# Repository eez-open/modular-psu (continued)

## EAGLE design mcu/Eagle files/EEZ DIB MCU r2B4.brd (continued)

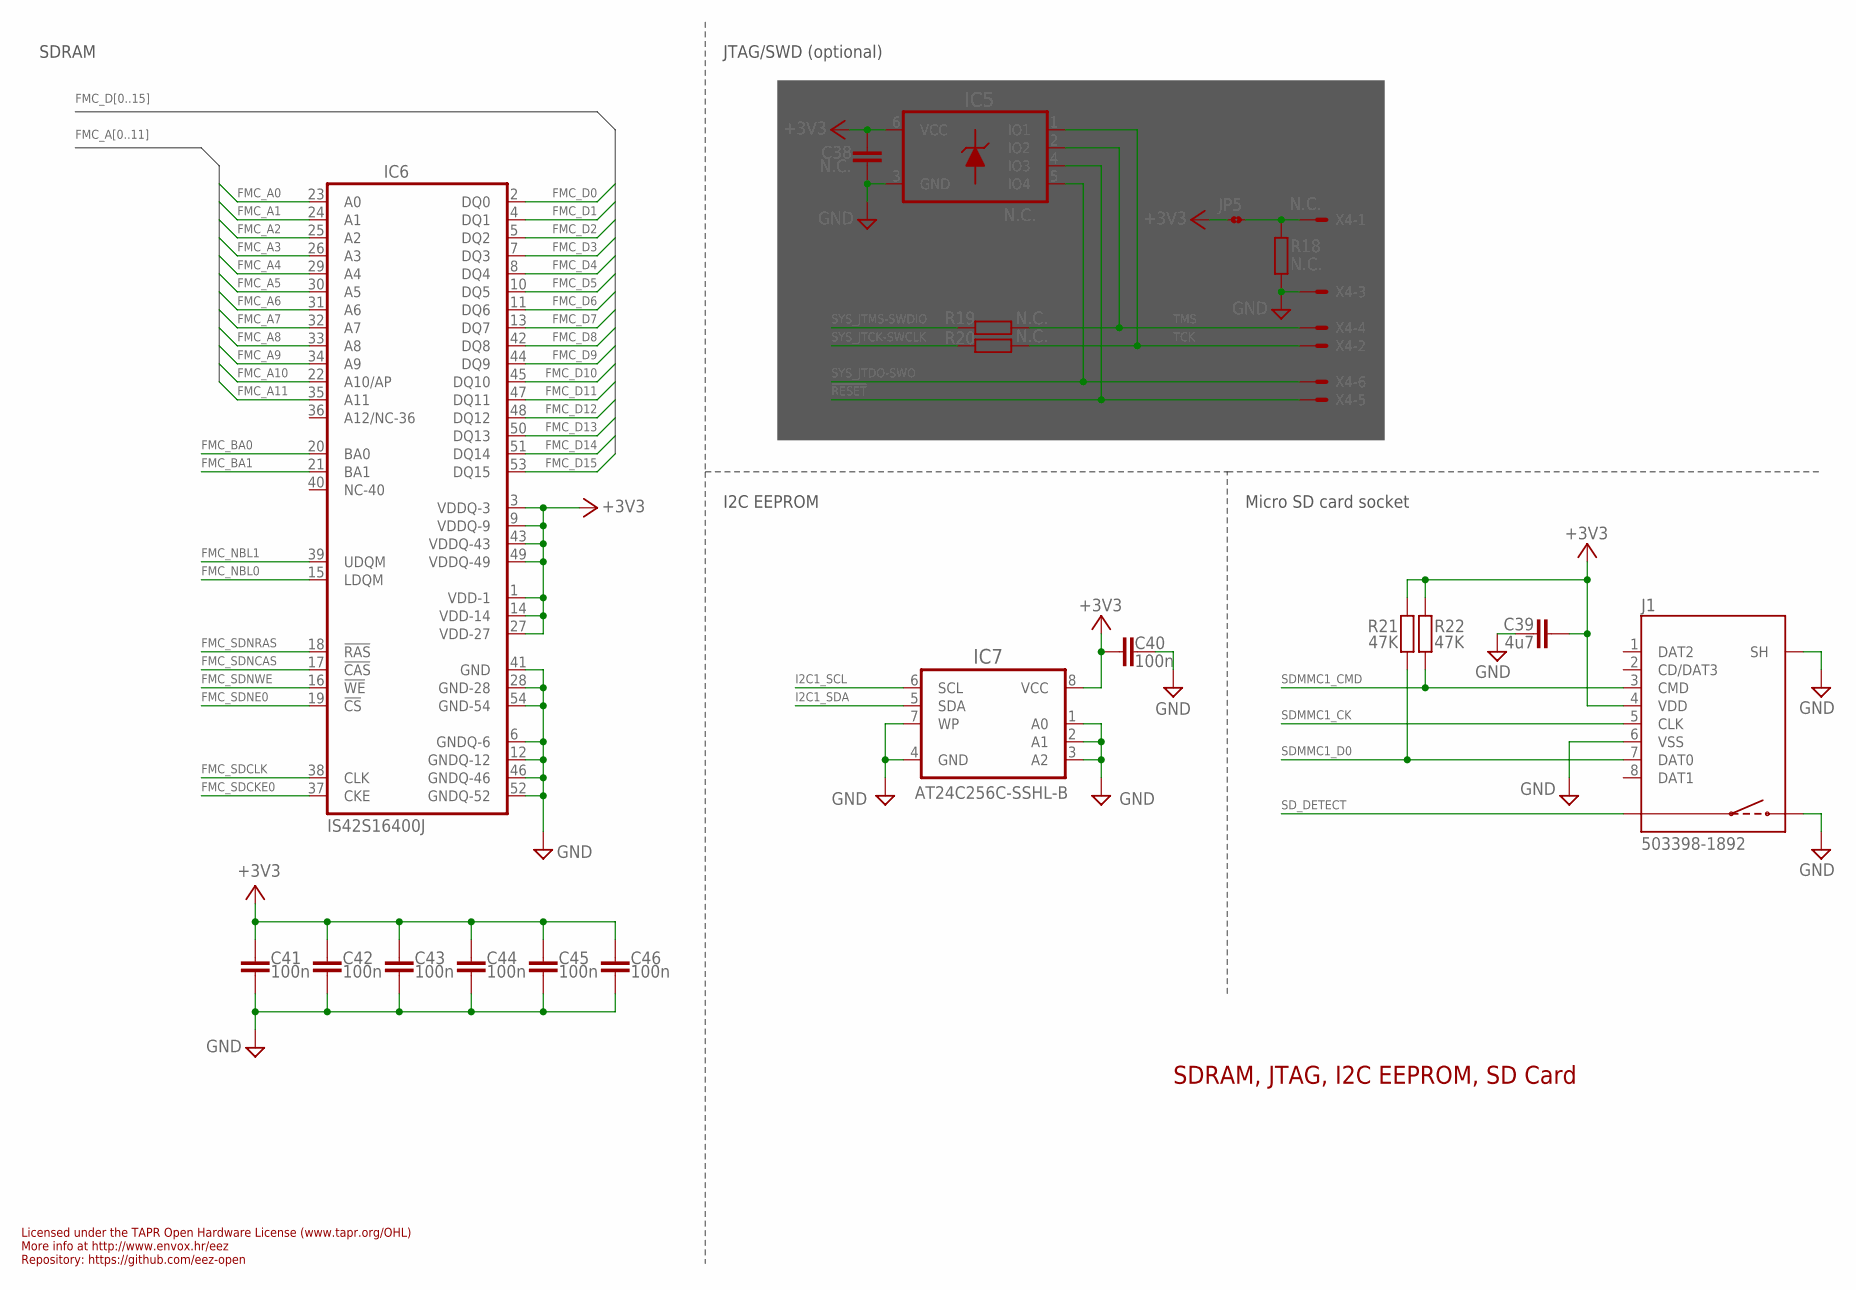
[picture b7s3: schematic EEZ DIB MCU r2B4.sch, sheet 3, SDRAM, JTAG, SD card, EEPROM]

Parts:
C38: N.C.; C0603
C39: 4u7; C1206
C40, C41, C42, C43, C44, C45, C46: 100n; C0603
IC5: N.C.; DRL6
IC6: IS42S16400J; TSOPII-54
IC7: AT24C256C-SSHL-B; SOIC127P600X173-8N
J1: 503398-1892; 5033981892
JP5: JP2-CUT
R18, R19, R20: N.C.; R0805
R21, R22: 47K; R0805
X4: N.C.; 22-23-2061

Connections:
!RESET: IC5.4 (IO3), X4.5; also elsewhere on the board
+3V3: C38.1, C39.1, C40.2, C41.1, C42.1, C43.1, C44.1, C45.1, C46.1, IC5.6 (VCC), IC6.1 (VDD-1), IC6.3 (VDDQ-3), IC6.9 (VDDQ-9), IC6.14 (VDD-14), IC6.27 (VDD-27), IC6.43 (VDDQ-43), IC6.49 (VDDQ-49), IC7.8 (VCC), J1.4 (VDD), JP5.1, R21.1, R22.1; also elsewhere on the board
FMC_A0: IC6.23 (A0); also elsewhere on the board
FMC_A1: IC6.24 (A1); also elsewhere on the board
FMC_A2: IC6.25 (A2); also elsewhere on the board
FMC_A3: IC6.26 (A3); also elsewhere on the board
FMC_A4: IC6.29 (A4); also elsewhere on the board
FMC_A5: IC6.30 (A5); also elsewhere on the board
FMC_A6: IC6.31 (A6); also elsewhere on the board
FMC_A7: IC6.32 (A7); also elsewhere on the board
FMC_A8: IC6.33 (A8); also elsewhere on the board
FMC_A9: IC6.34 (A9); also elsewhere on the board
FMC_A10: IC6.22 (A10/AP); also elsewhere on the board
FMC_A11: IC6.35 (A11); also elsewhere on the board
FMC_BA0: IC6.20 (BA0); also elsewhere on the board
FMC_BA1: IC6.21 (BA1); also elsewhere on the board
FMC_D0: IC6.2 (DQ0); also elsewhere on the board
FMC_D1: IC6.4 (DQ1); also elsewhere on the board
FMC_D2: IC6.5 (DQ2); also elsewhere on the board
FMC_D3: IC6.7 (DQ3); also elsewhere on the board
FMC_D4: IC6.8 (DQ4); also elsewhere on the board
FMC_D5: IC6.10 (DQ5); also elsewhere on the board
FMC_D6: IC6.11 (DQ6); also elsewhere on the board
FMC_D7: IC6.13 (DQ7); also elsewhere on the board
FMC_D8: IC6.42 (DQ8); also elsewhere on the board
FMC_D9: IC6.44 (DQ9); also elsewhere on the board
FMC_D10: IC6.45 (DQ10); also elsewhere on the board
FMC_D11: IC6.47 (DQ11); also elsewhere on the board
FMC_D12: IC6.48 (DQ12); also elsewhere on the board
FMC_D13: IC6.50 (DQ13); also elsewhere on the board
FMC_D14: IC6.51 (DQ14); also elsewhere on the board
FMC_D15: IC6.53 (DQ15); also elsewhere on the board
FMC_NBL0: IC6.15 (LDQM); also elsewhere on the board
FMC_NBL1: IC6.39 (UDQM); also elsewhere on the board
FMC_SDCKE0: IC6.37 (CKE); also elsewhere on the board
FMC_SDCLK: IC6.38 (CLK); also elsewhere on the board
FMC_SDNCAS: IC6.17 (!CAS); also elsewhere on the board
FMC_SDNE0: IC6.19 (!CS); also elsewhere on the board
FMC_SDNRAS: IC6.18 (!RAS); also elsewhere on the board
FMC_SDNWE: IC6.16 (!WE); also elsewhere on the board
GND: C38.2, C39.2, C40.1, C41.2, C42.2, C43.2, C44.2, C45.2, C46.2, IC5.3 (GND), IC6.6 (GNDQ-6), IC6.12 (GNDQ-12), IC6.28 (GND-28), IC6.41 (GND), IC6.46 (GNDQ-46), IC6.52 (GNDQ-52), IC6.54 (GND-54), IC7.1 (A0), IC7.2 (A1), IC7.3 (A2), IC7.4 (GND), IC7.7 (WP), J1.6 (VSS), J1.S (SH), J1.S1 (SH), J1.S2 (SH), J1.SW2, R18.1, X4.3; also elsewhere on the board
I2C1_SCL: IC7.6 (SCL); also elsewhere on the board
I2C1_SDA: IC7.5 (SDA); also elsewhere on the board
unnamed: JP5.2, R18.2, X4.1
SDMMC1_CK: J1.5 (CLK); also elsewhere on the board
SDMMC1_CMD: J1.3 (CMD), R22.2; also elsewhere on the board
SDMMC1_D0: J1.7 (DAT0), R21.2; also elsewhere on the board
SD_DETECT: J1.SW1; also elsewhere on the board
SYS_JTCK-SWCLK: R20.1; also elsewhere on the board
SYS_JTDO-SWO: IC5.5 (IO4), X4.6; also elsewhere on the board
SYS_JTMS-SWDIO: R19.1; also elsewhere on the board
TCK: IC5.1 (IO1), R20.2, X4.2
TMS: IC5.2 (IO2), R19.2, X4.4

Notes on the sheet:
SDRAM, JTAG, I2C EEPROM, SD Card
Licensed under the TAPR Open Hardware License (www.tapr.org/OHL)
Repository: https://github.com/eez-open
More info at http://www.envox.hr/eez
I2C EEPROM
Micro SD card socket
JTAG/SWD (optional)
SDRAM

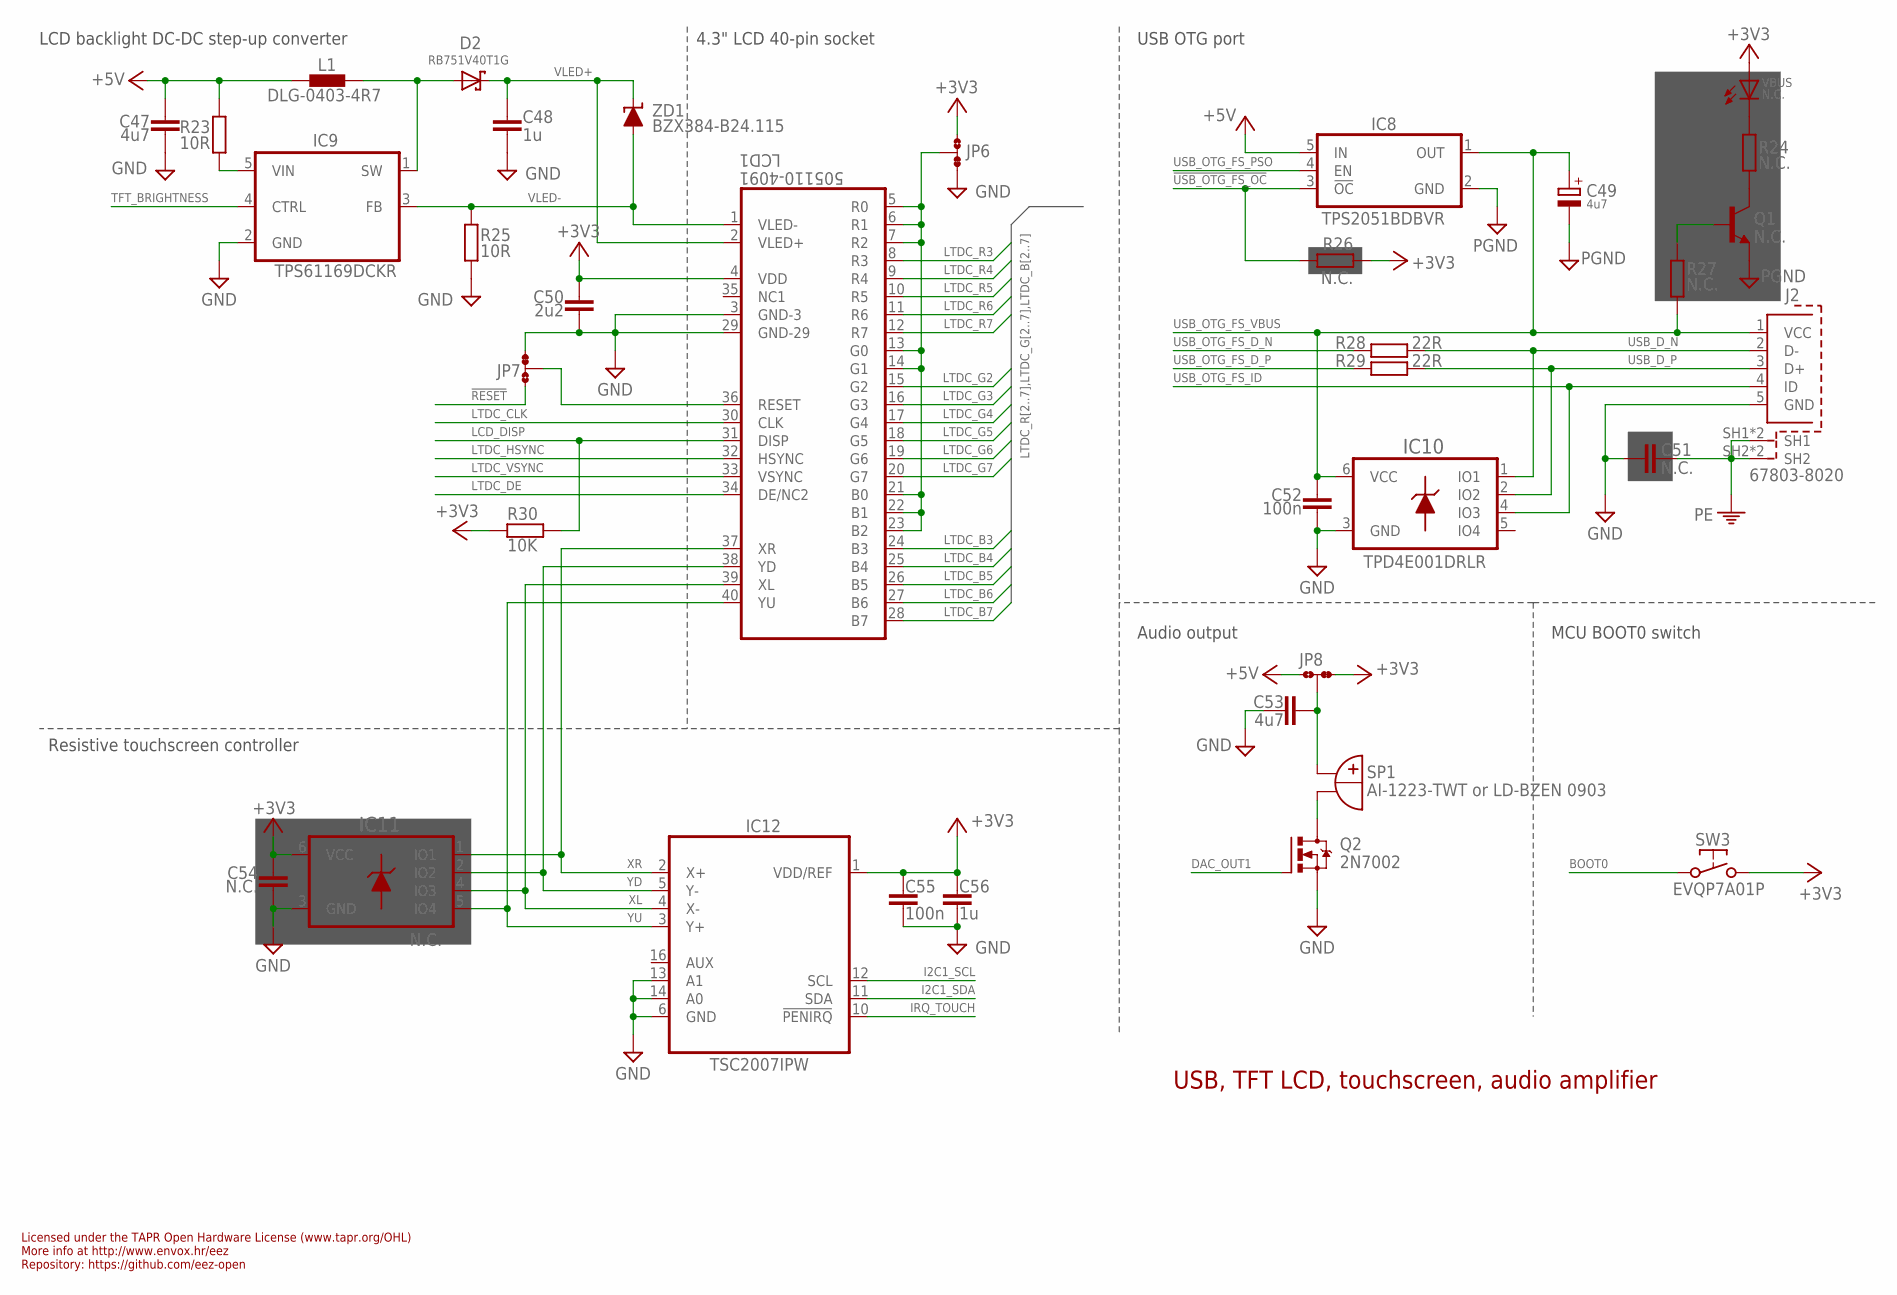
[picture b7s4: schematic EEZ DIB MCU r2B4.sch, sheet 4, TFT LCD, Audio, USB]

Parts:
C47, C53: 4u7; C1206
C48, C56: 1u; C0805
C49: 4u7; EC1206
C50: 2u2; C0805
C51: N.C.; C0805
C52, C55: 100n; C0603
C54: N.C.; C0603
D2: RB751V40T1G; SOD323-R
IC8: TPS2051BDBVR; DBV5
IC9: TPS61169DCKR; DCK5
IC10: TPD4E001DRLR; DRL6
IC11: N.C.; DRL6
IC12: TSC2007IPW; PW(R-PDSO-G16)
J2: 67803-8020; 678038020
JP6, JP7, JP8: JP3-CUT
L1: DLG-0403-4R7; DE0403
LCD1: 505110-4091; FPC_40
Q1: N.C.; SOT23-BEC
Q2: 2N7002; SOT103P240X110-3N
R23, R25: 10R; R0805
R24, R26, R27: N.C.; R0805
R28, R29: 22R; R0805
R30: 10K; R0805
SP1: AI-1223-TWT or LD-BZEN 0903; AI-1223-TWT_COMBO
SW3: EVQP7A01P; PANASONIC_EVQP
VBUS: N.C.; LED_0805
ZD1: BZX384-B24.115; SOD323-W

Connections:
!RESET: JP7.NO; also elsewhere on the board
!USB_OTG_FS_OC: IC8.3 (!OC), R26.1; also elsewhere on the board
+3V3: C50.1, C54.2, C55.2, C56.2, IC11.6 (VCC), IC12.1 (VDD/REF), JP6.NO, JP8.NC, LCD1.4 (VDD), R26.2, R30.2, SW3.2.1 (2), SW3.2.2 (2), VBUS.A; also elsewhere on the board
+5V: C47.1, IC8.5 (IN), JP8.NO, L1.1, R23.1; also elsewhere on the board
BOOT0: SW3.1.1 (1), SW3.1.2 (1); also elsewhere on the board
DAC_OUT1: Q2.1 (G); also elsewhere on the board
GND: C47.2, C48.2, C49.-, C50.2, C51.2, C52.1, C53.1, C54.1, C55.1, C56.1, IC8.2 (GND), IC9.2 (GND), IC10.3 (GND), IC11.3 (GND), IC12.6 (GND), IC12.13 (A1), IC12.14 (A0), J2.5 (GND), JP6.NC, JP7.NC, LCD1.3 (GND-3), LCD1.29 (GND-29), Q1.E, Q2.2 (S), R25.2; also elsewhere on the board
I2C1_SCL: IC12.12 (SCL); also elsewhere on the board
I2C1_SDA: IC12.11 (SDA); also elsewhere on the board
IRQ_TOUCH: IC12.10 (!PENIRQ); also elsewhere on the board
LCD_DISP: LCD1.31 (DISP), R30.1
LTDC_B3: LCD1.24 (B3); also elsewhere on the board
LTDC_B4: LCD1.25 (B4); also elsewhere on the board
LTDC_B5: LCD1.26 (B5); also elsewhere on the board
LTDC_B6: LCD1.27 (B6); also elsewhere on the board
LTDC_B7: LCD1.28 (B7); also elsewhere on the board
LTDC_CLK: LCD1.30 (CLK); also elsewhere on the board
LTDC_DE: LCD1.34 (DE/NC2); also elsewhere on the board
LTDC_G2: LCD1.15 (G2); also elsewhere on the board
LTDC_G3: LCD1.16 (G3); also elsewhere on the board
LTDC_G4: LCD1.17 (G4); also elsewhere on the board
LTDC_G5: LCD1.18 (G5); also elsewhere on the board
LTDC_G6: LCD1.19 (G6); also elsewhere on the board
LTDC_G7: LCD1.20 (G7); also elsewhere on the board
LTDC_HSYNC: LCD1.32 (HSYNC); also elsewhere on the board
LTDC_R3: LCD1.8 (R3); also elsewhere on the board
LTDC_R4: LCD1.9 (R4); also elsewhere on the board
LTDC_R5: LCD1.10 (R5); also elsewhere on the board
LTDC_R6: LCD1.11 (R6); also elsewhere on the board
LTDC_R7: LCD1.12 (R7); also elsewhere on the board
LTDC_VSYNC: LCD1.33 (VSYNC); also elsewhere on the board
unnamed: R24.2, VBUS.C
unnamed: JP6.COM, LCD1.5 (R0), LCD1.6 (R1), LCD1.7 (R2), LCD1.13 (G0), LCD1.14 (G1), LCD1.21 (B0), LCD1.22 (B1), LCD1.23 (B2)
unnamed: Q2.3 (D), SP1.-B (-), SP1.-B.1 (-)
unnamed: Q1.C, R24.1
unnamed: Q1.B, R27.2
unnamed: JP7.COM, LCD1.36 (RESET)
unnamed: IC9.5 (VIN), R23.2
unnamed: C53.2, JP8.COM, SP1.+B (+), SP1.+B.1 (+)
PE: C51.1, J2.SH1, J2.SH1.1 (SH1), J2.SH2, J2.SH2.2 (SH2); also elsewhere on the board
SW_WLED: D2.A, IC9.1 (SW), L1.2
TFT_BRIGHTNESS: IC9.4 (CTRL); also elsewhere on the board
USB_D_N: IC10.1 (IO1), J2.2 (D-), R28.1
USB_D_P: IC10.2 (IO2), J2.3 (D+), R29.1
USB_OTG_FS_D_N: R28.2; also elsewhere on the board
USB_OTG_FS_D_P: R29.2; also elsewhere on the board
USB_OTG_FS_ID: IC10.4 (IO3), J2.4 (ID); also elsewhere on the board
USB_OTG_FS_PSO: IC8.4 (EN); also elsewhere on the board
USB_OTG_FS_VBUS: C49.+, C52.2, IC8.1 (OUT), IC10.6 (VCC), J2.1 (VCC), R27.1; also elsewhere on the board
VLED+: C48.1, D2.C, LCD1.2 (VLED+), ZD1.C
VLED-: IC9.3 (FB), LCD1.1 (VLED-), R25.1, ZD1.A
XL: IC11.4 (IO3), IC12.4 (X-), LCD1.39 (XL)
XR: IC11.1 (IO1), IC12.2 (X+), LCD1.37 (XR)
YD: IC11.2 (IO2), IC12.5 (Y-), LCD1.38 (YD)
YU: IC11.5 (IO4), IC12.3 (Y+), LCD1.40 (YU)

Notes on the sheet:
USB, TFT LCD, touchscreen, audio amplifier
Licensed under the TAPR Open Hardware License (www.tapr.org/OHL)
Repository: https://github.com/eez-open
More info at http://www.envox.hr/eez
4.3" LCD 40-pin socket
LCD backlight DC-DC step-up converter
USB OTG port
Resistive touchscreen controller
Audio output
MCU BOOT0 switch

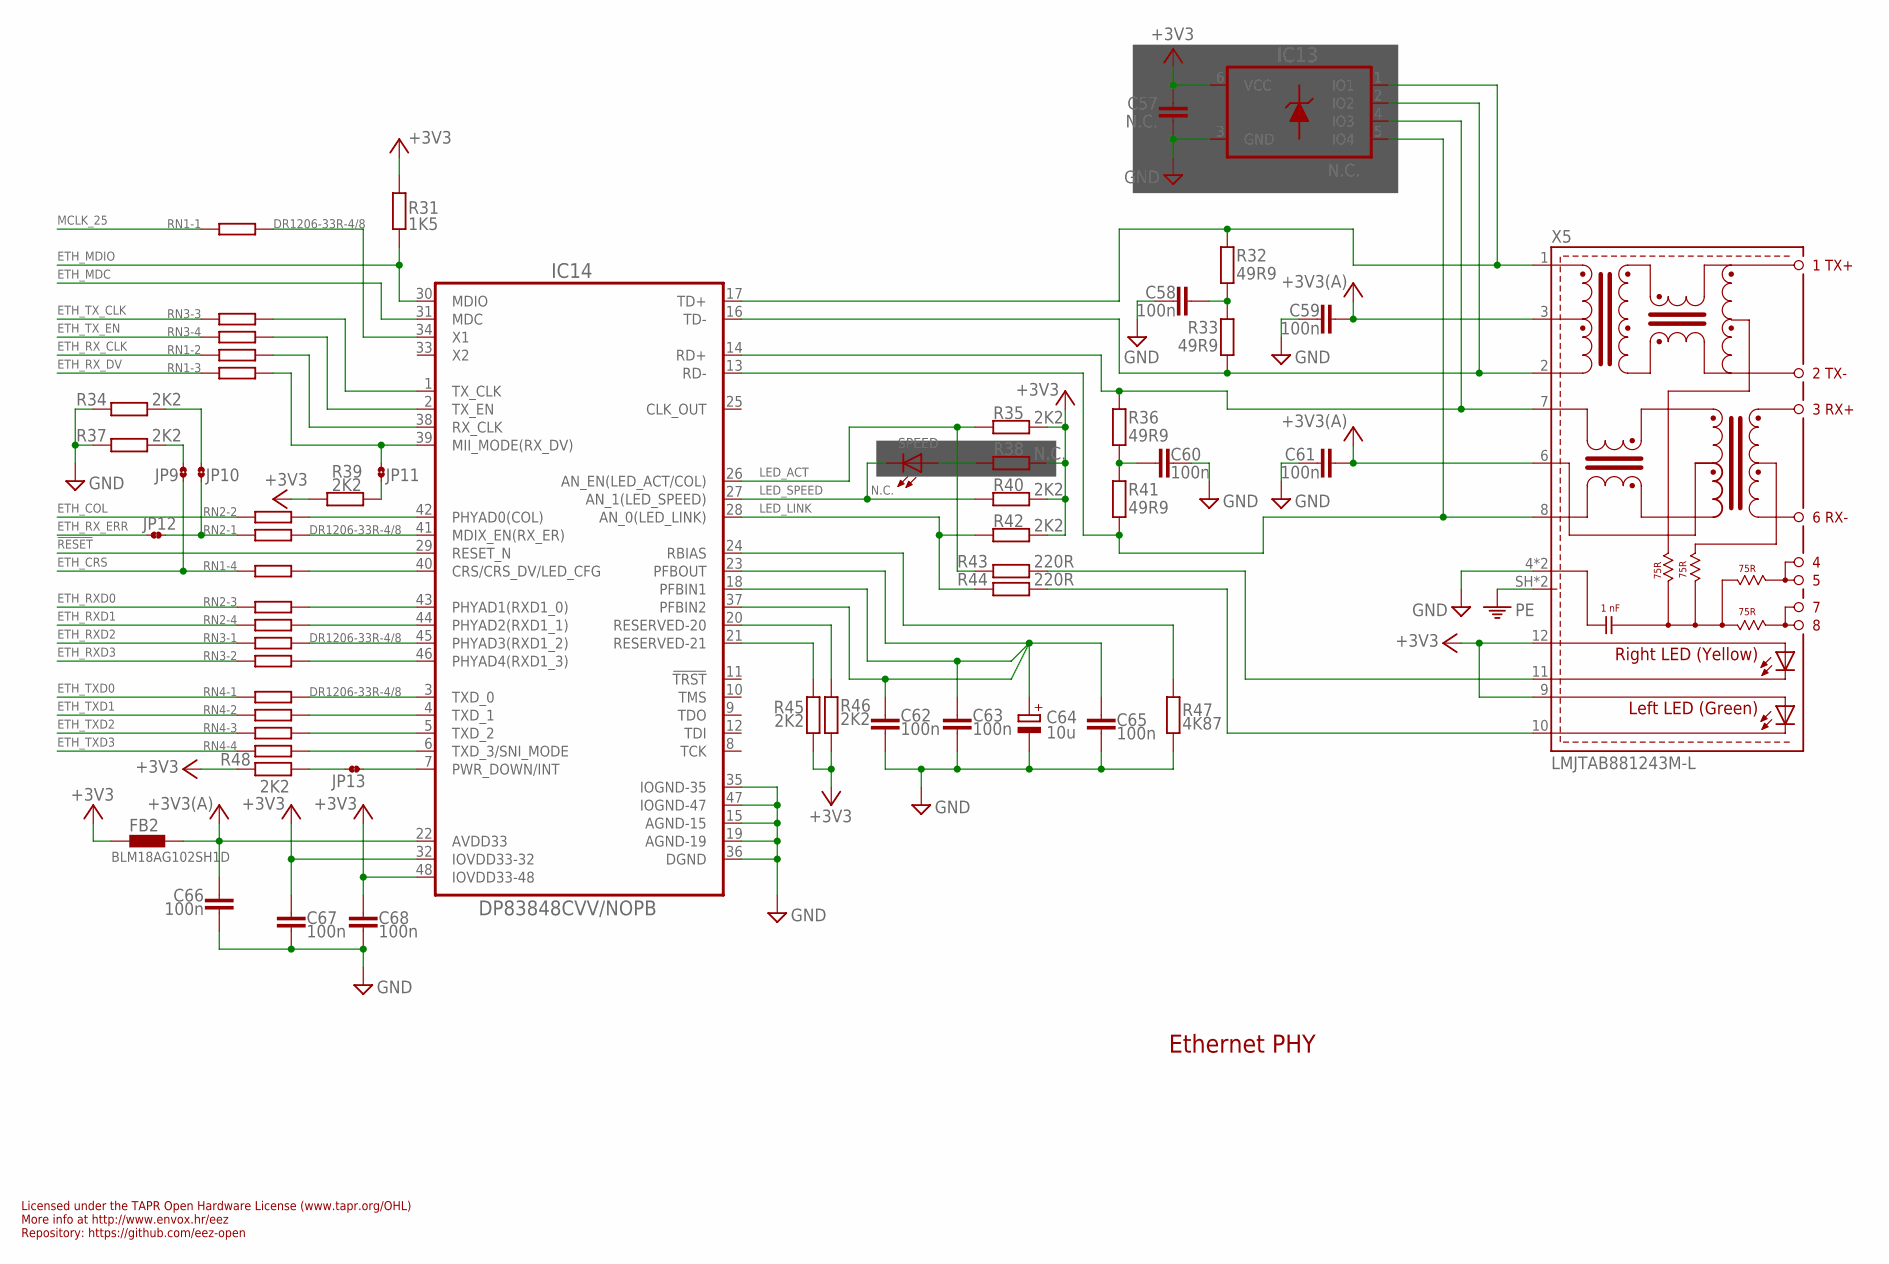
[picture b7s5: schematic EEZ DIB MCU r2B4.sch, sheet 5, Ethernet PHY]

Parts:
C57: N.C.; C0603
C58, C59, C60, C61, C62, C63, C65, C66, C67, C68: 100n; C0603
C64: 10u; EC1206
FB2: BLM18AG102SH1D; BEAD0603
IC13: N.C.; DRL6
IC14: DP83848CVV/NOPB; PT48
JP9, JP10, JP11: JP2-CUT
JP12, JP13: JP2-NOCUT
R31: 1K5; R0805
R32, R33, R36, R41: 49R9; R0805
R34, R35, R37, R39, R40, R42, R45, R46, R48: 2K2; R0805
R38: N.C.; R0805
R43, R44: 220R; R0805
R47: 4K87; R0805
RN1, RN2, RN3, RN4: DR1206-33R-4/8; CAY16
SPEED: N.C.; LED_0805
X5: LMJTAB881243M-L; RJ45-TRAFO-LED

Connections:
!RESET: IC14.29 (RESET_N); also elsewhere on the board
+3V3: C57.1, C67.1, C68.1, FB2.P$1 (1), IC13.6 (VCC), IC14.32 (IOVDD33-32), IC14.48 (IOVDD33-48), R31.2, R35.1, R38.1, R39.1, R40.1, R42.1, R45.1, R46.1, R48.1, X5.9 (GREEN-A), X5.12 (YELLOW_A); also elsewhere on the board
+3V3(A): C59.2, C61.2, C66.1, FB2.P$2 (2), IC14.22 (AVDD33), X5.3 (CT), X5.6 (CR)
ETH_COL: RN2.2 (1); also elsewhere on the board
ETH_CRS: JP9.1, RN1.4 (1); also elsewhere on the board
ETH_MDC: IC14.31 (MDC); also elsewhere on the board
ETH_MDIO: IC14.30 (MDIO), R31.1; also elsewhere on the board
ETH_RXD0: RN2.3 (1); also elsewhere on the board
ETH_RXD1: RN2.4 (1); also elsewhere on the board
ETH_RXD2: RN3.1; also elsewhere on the board
ETH_RXD3: RN3.2 (1); also elsewhere on the board
ETH_RX_CLK: RN1.2 (1); also elsewhere on the board
ETH_RX_DV: RN1.3 (1); also elsewhere on the board
ETH_RX_ER: JP10.1, JP12.1, RN2.1
ETH_RX_ERR: JP12.2; also elsewhere on the board
ETH_TXD0: RN4.1; also elsewhere on the board
ETH_TXD1: RN4.2 (1); also elsewhere on the board
ETH_TXD2: RN4.3 (1); also elsewhere on the board
ETH_TXD3: RN4.4 (1); also elsewhere on the board
ETH_TX_CLK: RN3.3 (1); also elsewhere on the board
ETH_TX_EN: RN3.4 (1); also elsewhere on the board
GND: C57.2, C58.2, C59.1, C60.2, C61.1, C62.2, C63.2, C64.-, C65.2, C66.2, C67.2, C68.2, IC13.3 (GND), IC14.15 (AGND-15), IC14.19 (AGND-19), IC14.35 (IOGND-35), IC14.36 (DGND), IC14.47 (IOGND-47), R34.1, R37.1, R47.1, X5.4 (GND), X5.5 (GND); also elsewhere on the board
LED_ACT: IC14.26 (AN_EN(LED_ACT/COL)), R35.2, R43.2
LED_LINK: IC14.28 (AN_0(LED_LINK)), R42.2, R44.2
LED_SPEED: IC14.27 (AN_1(LED_SPEED)), R40.2, SPEED.C
MCLK_25: RN1.1; also elsewhere on the board
unnamed: IC14.1 (TX_CLK), RN3.6 (2)
unnamed: C58.1, R32.1, R33.2
unnamed: R43.1, X5.11 (YELLOW-C)
unnamed: R44.1, X5.10 (GREEN-C)
unnamed: IC14.2 (TX_EN), RN3.5 (2)
unnamed: IC14.39 (MII_MODE(RX_DV)), JP11.2, RN1.6 (2)
unnamed: IC14.38 (RX_CLK), RN1.7 (2)
unnamed: IC14.3 (TXD_0), RN4.8 (2)
unnamed: IC14.4 (TXD_1), RN4.7 (2)
unnamed: IC14.5 (TXD_2), RN4.6 (2)
unnamed: IC14.34 (X1), RN1.8 (2)
unnamed: JP11.1, R39.2
unnamed: JP9.2, R37.2
unnamed: JP10.2, R34.2
unnamed: IC14.7 (PWR_DOWN/INT), JP13.2
unnamed: JP13.1, R48.2
unnamed: IC14.6 (TXD_3/SNI_MODE), RN4.5 (2)
unnamed: IC14.46 (PHYAD4(RXD1_3)), RN3.7 (2)
unnamed: IC14.45 (PHYAD3(RXD1_2)), RN3.8 (2)
unnamed: IC14.42 (PHYAD0(COL)), RN2.7 (2)
unnamed: IC14.44 (PHYAD2(RXD1_1)), RN2.5 (2)
unnamed: IC14.43 (PHYAD1(RXD1_0)), RN2.6 (2)
unnamed: IC14.41 (MDIX_EN(RX_ER)), RN2.8 (2)
unnamed: IC14.40 (CRS/CRS_DV/LED_CFG), RN1.5 (2)
unnamed: IC14.24 (RBIAS), R47.2
unnamed: IC14.21 (RESERVED-21), R45.2
unnamed: IC14.20 (RESERVED-20), R46.2
unnamed: R38.2, SPEED.A
unnamed: C60.1, R36.1, R41.2
PE: X5.SH, X5.SH2 (SH); also elsewhere on the board
PFBOUT: C62.1, C63.1, C64.+, C65.1, IC14.18 (PFBIN1), IC14.23 (PFBOUT), IC14.37 (PFBIN2)
RD+: IC13.4 (IO3), IC14.14 (RD+), R36.2, X5.7 (RD+)
RD-: IC13.5 (IO4), IC14.13 (RD-), R41.1, X5.8 (RD-)
TD+: IC13.1 (IO1), IC14.17 (TD+), R32.2, X5.1 (TD+)
TD-: IC13.2 (IO2), IC14.16 (TD-), R33.1, X5.2 (TD-)

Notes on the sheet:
Ethernet PHY
Licensed under the TAPR Open Hardware License (www.tapr.org/OHL)
Repository: https://github.com/eez-open
More info at http://www.envox.hr/eez

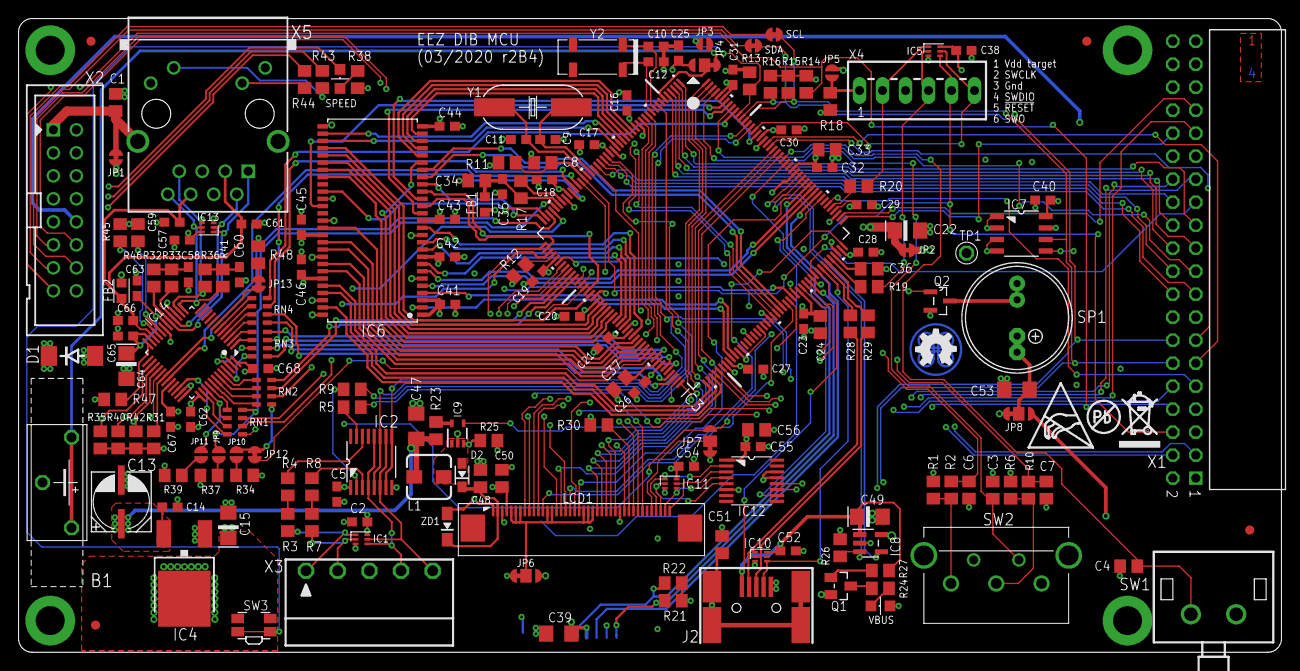
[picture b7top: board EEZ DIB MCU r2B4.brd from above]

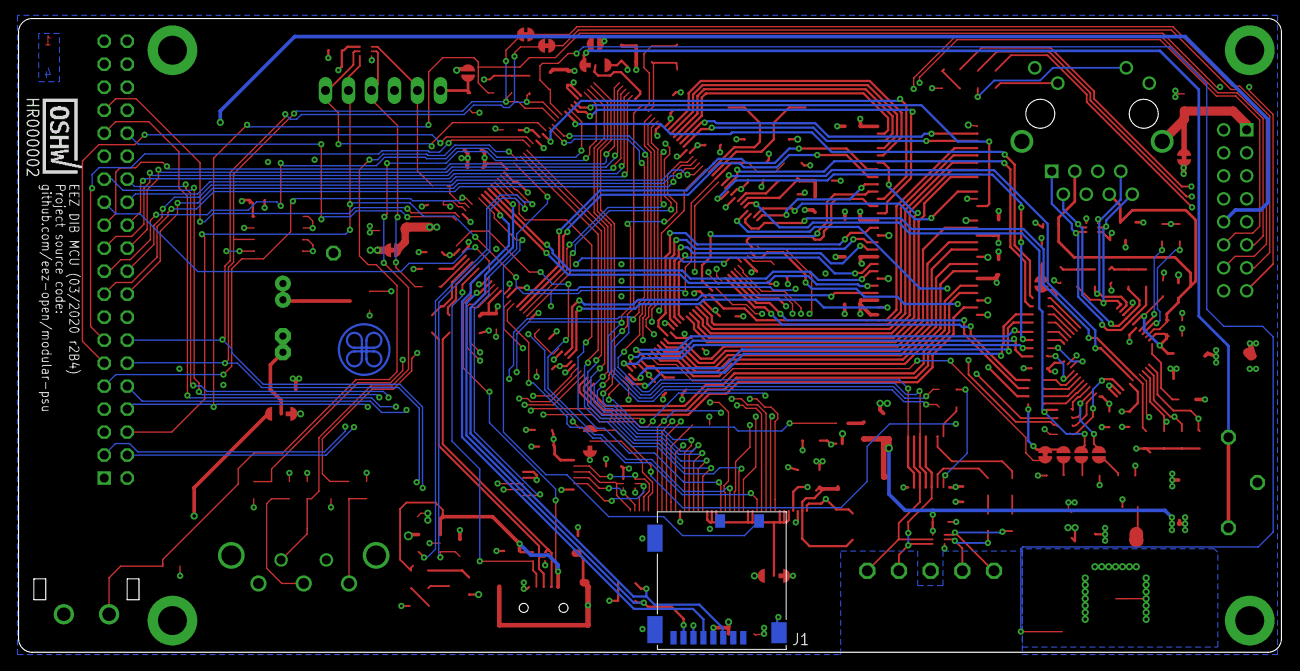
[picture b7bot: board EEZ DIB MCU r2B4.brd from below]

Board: 4 copper layers, 139.5 x 70.0 mm, 184 parts (2 on the bottom side), 219 nets.

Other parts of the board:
EEZ_SIGNATURE: SIGNATURESMALL; SIGNATURE_5MM
U$1: RECYCLE_BIN1/8
U$5: PB_SMALL
U$6: ESD_SYMBOL

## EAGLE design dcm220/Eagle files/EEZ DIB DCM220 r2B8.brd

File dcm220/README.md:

### Overview
---
**RETIRED - Left as a reference for Crowd Supply [campaign](https://www.crowdsupply.com/envox/eez-bb3) backers. For the current version please visit the [DCM224](https://github.com/eez-open/dib-dcm224) repository.**
---
The EEZ DIB DCM220 Power module features dual sync buck converters based on [LT3763](https://www.analog.com/en/products/lt3763.html) with programmable output voltage and current limit.

### Feature list
- On-board STM32F373 MCU
Power input: 48 Vdc (e.g. Mean Well LRS-150F-48)
- Max. output power: up to 2 x 80 W
- Voltage regulation (CV), 1 – 20 V. Voltage set resolution (_U_SET_): 12-bit, read resolution (_U_MON_): 15-bit
- Current regulation (CC), 0.3 – 4 A. Current set resolution (_I_SET_): 12-bit, Current read resolution (_I_MON_): 15-bit
- On-board power pre-regulator and bias power supply
- Output Enable (_OE_) and Constant Current mode (_CC_) LED indications
- Output LC filter for improved ripple and noise
- On-board 4 mm power output terminals with standard (19.05 mm) pitch
- Pass-thru connector for Vout- coupling with other DIB power modules
- Galvanically isolated SPI bus for communication with [MCU board](https://github.com/eez-open/modular-psu/tree/master/mcu)
- I2C EEPROM for storing board specific configuration and calibration parameters
- Dimensions: 155 x 95 mm, 2-layer PCB

### Firmware repository

https://github.com/eez-open/dib-dcm220-fw
The firmware download procedure is described in the User Manual in [Chapter 13](https://github.com/eez-open/modular-psu/blob/master/docs/user%20manual/EEZ%20BB3%20user%20manual.pdf).

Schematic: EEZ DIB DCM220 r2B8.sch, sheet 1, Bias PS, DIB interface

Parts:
C1, C2, C3: 10n/200V; C1206
C4, C5, C14: 4u7; C1206
C6, C9, C21: 2u2; C1206
C7, C8, C10, C17, C18, C20: 100n; C0603
C11: 330p; C0805
C12: 22u; C1206
C13: N.C.; C1206
C15, C19, C23: 10n; C0805
C16: 33p; C0603
C22: N.C.; C0805
D1, D2: SKL16; SOD123
FM1, FM2: FIDUCIAL_2; FIDUCIAL_DUAL
IC1: Si8662AB-B-IS1; SOIC-16
IC2: TPS54060DGQ; SOP50P490X110-11N
IC3: Si8641AB-B-IS1; SOIC-16
IC4: M24C32-WMN6P; SOIC127P600X173-8N
IC5: LP2985-33DBVR; SOT95P270X145-5N
J1: 4907; PCB_TAB-4907
KK1, KK2: PMB-1; PCB-MB
L1: RN112-4-02-0M7; RN112
R1: N.C.; R2512
R2, R4, R5: 10R; R0805
R3: 47K; R0805
R6: 2K2; R0805
R7, R9: 86K6; R0805
R8: 330K; R0805
R10, R11, R12, R13: 10K; R0805
RN1: DR1206-33R-4/8; CAY16
TR1: SRF0703-821M; SRF0703
TX_PU: 10K; R0805
U$3: HR000002; CERT-SMALL-SILK
X1: 39-30-1020; MINIFIT_39301020
X2: 77317-104-28LF
ZD1: SMAJ51A; DO214AA

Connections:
!RESET: IC1.15 (B1); also elsewhere on the board
+3V3: C8.2, C18.2, C21.1, IC1.16 (VDD2), IC3.10 (EN2), IC3.16 (VDD2), IC5.5 (OUT), TX_PU.2; also elsewhere on the board
+8V: C14.1, C22.2, IC5.1 (IN), IC5.3 (ON/!OFF), R4.1; also elsewhere on the board
+VAUX: X2.2
-8V: C5.1, R2.1; also elsewhere on the board
BOOT0: IC3.13 (B2); also elsewhere on the board
DC+: C1.2, L1.3 (1), R1.2, X1.1
DC-: C1.1, L1.1, R1.1, X1.2
DC_OUT+: C3.2, C6.1, C9.1, IC2.2 (VIN), L1.4 (2), R3.2, ZD1.C; also elsewhere on the board
DIB_A0: IC4.1 (A0), R13.2, X2.17
DIB_A1: IC4.2 (A1), R12.2, X2.19
DIB_A2: IC4.3 (A2), R11.2, X2.18
DIB_BOOT0: IC3.4 (A2), IC3.7 (EN1), X2.26
DIB_CSA: IC1.5 (A4), X2.9
DIB_CSB: X2.12
DIB_IRQ: IC1.7 (A6), X2.10
DIB_MISO: IC1.6 (A5), X2.14
DIB_MOSI: IC3.3 (A1), X2.15
DIB_NFAULT: X2.3
DIB_NRESET: IC1.2 (A1), X2.4
DIB_SCL: IC4.6 (SCL), X2.5
DIB_SCLK: IC1.4 (A3), X2.13
DIB_SDA: IC4.5 (SDA), X2.8
DIB_SYNC: IC1.3 (A2), X2.6
DIB_UART_RX: IC3.6 (A4), X2.27
DIB_UART_TX: IC3.5 (A3), X2.28
GND: C2.1, C4.2, C5.2, C6.2, C8.1, C9.2, C12.2, C13.2, C14.2, C15.2, C16.1, C18.1, C19.1, C21.2, C22.1, C23.1, D2.A, IC1.9 (GND2), IC2.9 (GND), IC2.TP, IC3.9 (GND2_2), IC3.15 (GND2), IC5.2 (GND), L1.2, R5.1, R6.1, R8.1, R10.1, TR1.4, ZD1.A; also elsewhere on the board
GNDIO: C7.2, C17.2, C20.1, IC1.8 (GND1), IC3.2 (GND1_2), IC3.8 (GND1), IC4.4 (GND), IC4.7 (WP), X2.7, X2.11, X2.16, X2.20, X2.25
IRQ: IC1.10 (B6); also elsewhere on the board
MISO: IC1.11 (B5); also elsewhere on the board
MOSI: RN1.5 (2); also elsewhere on the board
unnamed: IC1.14 (B2), RN1.1
unnamed: IC1.13 (B3), RN1.2 (1)
unnamed: IC1.12 (B4), RN1.3 (1)
unnamed: IC3.14 (B1), RN1.4 (1)
unnamed: C23.2, IC5.4 (BYPASS)
unnamed: C4.1, D1.A, R2.2
unnamed: C11.2, R5.2
unnamed: IC2.3 (EN), R3.1, R6.2
unnamed: C15.1, IC2.4 (SS/TR)
unnamed: IC2.5 (RT/CLK), R8.2
unnamed: C16.2, IC2.8 (COMP), R9.2
unnamed: C19.2, R9.1
unnamed: C10.2, IC2.1 (BOOT)
unnamed: IC2.7 (VSENSE), R7.1, R10.2
NSS: RN1.6 (2); also elsewhere on the board
OE_SYNC: RN1.8 (2); also elsewhere on the board
PE: C2.2, C3.1, J1.1, J1.2; also elsewhere on the board
PH1: C10.1, C11.1, D2.C, IC2.10 (PH), TR1.1
PWRGOOD: IC2.6 (PWRGD); also elsewhere on the board
SCLK: RN1.7 (2); also elsewhere on the board
UART_RX: IC3.12 (B3); also elsewhere on the board
UART_TX: IC3.11 (B4), TX_PU.1; also elsewhere on the board
V+: C7.1, C17.1, C20.2, IC1.1 (VDD1), IC3.1 (VDD1), IC4.8 (VCC), R11.1, R12.1, R13.1, X2.1
VOUT+: C12.1, C13.1, R4.2, R7.2, TR1.3
VOUT-: D1.C, TR1.2

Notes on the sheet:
Licensed under the TAPR Open Hardware License (www.tapr.org/OHL)
Repository: https://github.com/eez-open
More info at http://www.envox.hr/eez
I2C Module ID EEPROM
Bias power supply, I2C EEPROM, digital isolators
Plastic parts
Bus isolator
+3V3 LDO
DIB v1.0 connector
Bias power supply
+48V DC input

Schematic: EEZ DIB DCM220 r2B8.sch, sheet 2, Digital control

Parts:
C24, C26, C27, C28, C30, C31, C37, C40: 100n; C0603
C25, C32, C33: N.C.; C0603
C29: 4u7; C1206
C34, C35: 10n; C0805
C36: 1n; C0805
C38: 1u; C0805
C39, C41, C42, C43, C44: 4n7; C0805
FB1: 1K@100MHz; BEAD0603
IC6: 74HC2G04GW,125; SOT65P210X110-6N
IC7: N.C.; DRL6
IC8: STM32F373C8T6; LQFP-48
IC9: TL431B; SOT103P240X110-3N
I_SET1, I_SET2: JP2-NOCUT
JP1: JUMPER-2PIN-2MM; 2MM-2
JP2: JP2-CUT
JP3: JP2-NOCUT
NTC1, NTC2: NTCS0805E3103JMT; R_0805
OE#1, OE#2: JP2-NOCUT
R14, R15, R16, R17, R18, R20: 10K; R0805
R19: N.C.; R0805
R21, R22: 3K3; R0805
R23: 120R; R0805
R24, R25, R26, R27: 2K2; R0805
RN2: N.C.; CAY16
SH2: SHORTNOHOLE; SHORT_NOHOLE
U_SET1, U_SET2: JP2-NOCUT
X3: N.C.; 22-23-2061
Y1: N.C.; 12SMX(B)

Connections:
!RESET: JP3.1; also elsewhere on the board
+3V3: C25.1, C27.1, C28.2, C29.1, C36.2, C40.2, FB1.P$1 (1), IC6.5 (V+), IC7.6 (VCC), IC8.17 (VDD_2), IC8.48 (VDD_1), JP1.1, JP2.1, NTC1.1, NTC2.1, R20.1, R23.1; also elsewhere on the board
+VREF: C39.2, IC8.9 (VDDA/VREF+), IC8.25 (VREFSD+), IC9.1 (C), IC9.2 (R), R23.2
AGND: C39.1, IC8.8 (VSSA/VREF-), IC8.23 (VSSSD/VREFSD-), IC9.3 (A), SH2.1 (GND_A)
BOOT0: IC8.44 (BOOT0), JP1.2, R15.2; also elsewhere on the board
CC#1: IC8.3 (PC14-OSC32_IN); also elsewhere on the board
CC#2: IC8.4 (PC15-OSC32_OUT); also elsewhere on the board
CC_LED#1: IC8.2 (PC13); also elsewhere on the board
CC_LED#2: IC8.11 (PA1); also elsewhere on the board
GND: C25.2, C26.2, C27.2, C28.1, C29.2, C31.2, C32.1, C33.1, C34.1, C35.1, C37.1, C38.1, C40.1, C41.1, C42.1, C43.1, C44.1, IC6.2 (V-), IC7.3 (GND), IC8.47 (VSS_1), R15.1, R19.1, R21.2, R22.2, SH2.2 (GND_B), X3.3; also elsewhere on the board
IRQ: IC8.33 (PA12); also elsewhere on the board
I_MON1: R25.2; also elsewhere on the board
I_MON2: R27.2; also elsewhere on the board
I_MON#1: C42.2, IC8.19 (PB1), R25.1
I_MON#2: C44.2, IC8.21 (PE8), R27.1
I_SET#1: I_SET1.1; also elsewhere on the board
I_SET#2: I_SET2.1; also elsewhere on the board
I_SET_OUT#1: IC6.1 (I), IC8.45 (PB8), R14.2
I_SET_OUT#2: IC6.3 (I), IC8.46 (PB9), R17.2
MISO: IC8.26 (PB14); also elsewhere on the board
MOSI: IC8.27 (PB15); also elsewhere on the board
unnamed: C30.2, R18.1
unnamed: C30.1, C31.1, I_SET2.2, R17.1
unnamed: IC6.4 (O), R18.2
unnamed: IC7.1 (IO1), RN2.8 (2), X3.6
unnamed: IC7.2 (IO2), RN2.6 (2), X3.5
unnamed: JP2.2, R19.2, X3.1
unnamed: C24.2, R16.1
unnamed: C24.1, C26.1, I_SET1.2, R14.1
unnamed: IC6.6 (O), R16.2
unnamed: IC8.42 (PB6), OE#2.1
unnamed: IC8.41 (PB5), OE#1.1
NRST: C36.1, IC8.7 (NRST), JP3.2, R20.2, RN2.3 (1)
NSS: IC8.32 (PA11); also elsewhere on the board
OE#1: OE#1.2; also elsewhere on the board
OE#2: OE#2.2; also elsewhere on the board
OE_SYNC: IC8.36 (PF7); also elsewhere on the board
PWRGOOD: IC8.40 (PB4); also elsewhere on the board
RCC_OSC_IN: C32.2, IC8.5 (PF0-OSC_IN), Y1.3 (2)
RCC_OSC_OUT: C33.2, IC8.6 (PF1-OSC_OUT), Y1.1
SCLK: IC8.28 (PD8); also elsewhere on the board
SWCLK: IC8.37 (PA14), RN2.2 (1)
SWDIO: IC8.34 (PA13), RN2.4 (1)
SWO: IC8.39 (PB3), RN2.1
TCK: IC7.5 (IO4), RN2.7 (2), X3.2
TEMP#1: C34.2, IC8.10 (PA0), NTC1.2, R21.1
TEMP#2: C35.2, IC8.14 (PA4), NTC2.2, R22.1
TMS: IC7.4 (IO3), RN2.5 (2), X3.4
UART_RX: IC8.31 (PA10); also elsewhere on the board
UART_TX: IC8.30 (PA9); also elsewhere on the board
U_MON1: R24.2; also elsewhere on the board
U_MON2: R26.2; also elsewhere on the board
U_MON#1: C41.2, IC8.18 (PB0), R24.1
U_MON#2: C43.2, IC8.20 (PB2), R26.1
U_SET#1: U_SET1.1; also elsewhere on the board
U_SET#2: U_SET2.1; also elsewhere on the board
U_SET_OUT#1: IC8.16 (PA6), U_SET1.2
U_SET_OUT#2: IC8.15 (PA5), U_SET2.2
VDDA: C37.2, C38.2, FB1.P$2 (2), IC8.24 (VDDSD)

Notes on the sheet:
DAC, MCU, JTAG, ADC input section, temp. sensors
Optional JTAG (SWD)
MCU
Temperature sensors
ADC input RC filters
Voltage reference
